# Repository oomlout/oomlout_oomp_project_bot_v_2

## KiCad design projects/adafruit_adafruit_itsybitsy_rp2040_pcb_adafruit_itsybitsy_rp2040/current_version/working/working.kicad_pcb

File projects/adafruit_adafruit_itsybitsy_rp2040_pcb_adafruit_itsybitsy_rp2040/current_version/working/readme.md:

# adafruit_itsybitsy_rp2040_pcb
 
## summary 
* id: adafruit_adafruit_itsybitsy_rp2040_pcb_adafruit_itsybitsy_rp2040
* user: adafruit
* name: adafruit_itsybitsy_rp2040_pcb
* board: adafruit_itsybitsy_rp2040
* repo: https://github.com/adafruit/Adafruit-ItsyBitsy-RP2040-PCB

* src_file_repo_sch: 
* src_file_repo_sch_link: https://github.com/adafruit/Adafruit-ItsyBitsy-RP2040-PCB/tree/main/
* full details link: https://github.com/oomlout/oomlout_oomp_project_bot_v_2/tree/main/projects/adafruit_adafruit_itsybitsy_rp2040_pcb_adafruit_itsybitsy_rp2040/current_version/working  

## schematic  
  
[schematic (pdf)](working_schematic.pdf) 

## pcb  

[board (pdf)](working.pdf)  

## working_bom
| Id | Designator | Footprint | Quantity | Designation | Supplier and ref |  | None | 
| --- | --- | --- | --- | --- | --- | --- | --- | 
| 1 | C11,C2 | _0603MP | 2 | 1uF |  |  | [''] | 
| 2 | C10,C3,C4,C13,C16,C12 | _0402NO | 6 | 0.1uF |  |  | [''] | 
| 3 | IC3 | QFN56_7MM_REDUCEDEPAD | 1 | RP2040_QFN56 |  |  | [''] | 
| 4 | U$35,U$34 | FIDUCIAL_1MM | 2 | FIDUCIAL_1MM |  |  | [''] | 
| 5 | D3,D1,D2 | SOD-323F | 3 | NSR0320 |  |  | [''] | 
| 6 | R5,R1 | _0402NO | 2 | 10K |  |  | [''] | 
| 7 | R4,R3 | _0402NO | 2 | 22 |  |  | [''] | 
| 8 | C6,C8 | 0805-NO | 2 | 10ÂµF |  |  | [''] | 
| 9 | L0 | CHIPLED_0603_NOOUTLINE | 1 | RED |  |  | [''] | 
| 10 | U1 | USON8_4X4 | 1 | GD25x16 |  |  | [''] | 
| 11 | JP4,JP2 | 1X14_ROUND70 | 2 |  |  |  | [''] | 
| 12 | R2 | _0402NO | 1 | 10k |  |  | [''] | 
| 13 | IC1 | SC70-5 | 1 | 74HCT1G125DBV |  |  | [''] | 
| 14 | C20,C19 | _0402NO | 2 | 22pF |  |  | [''] | 
| 15 | R11,R6,R7 | _0402NO | 3 | 1K |  |  | [''] | 
| 16 | U$4 | ITSY2040_TOP | 1 |  |  |  | [''] | 
| 17 | Y1 | CRYSTAL_2.5X2 | 1 | 12MHZ |  |  | [''] | 
| 18 | X3 | 4UCONN_20329_NARROW | 1 | microUSB |  |  | [''] | 
| 19 | SW3,SW2 | BTN_KMR2_4.6X2.8 | 2 | KMR2 |  |  | [''] | 
| 20 | U2 | SOT23-5 | 1 | AP2112K-3.3 |  |  | [''] | 
| 21 | JP1 | 1X05_ROUND_70 | 1 |  |  |  | [''] | 
| 22 | LED1 | SK6805_1515 | 1 | WS2812B_SK6805_1515 |  |  | [''] | 
| 23 | TP1 | TESTPOINT_ROUND_1.5MM_NO | 1 |  |  |  | [''] | 
| 24 | U$5 | ITSY2040_BOT | 1 |  |  |  | [''] | 

## bom_schematic
| Ref | Qnty | Value | Cmp name | Footprint | Description | Vendor | DNP | 
| --- | --- | --- | --- | --- | --- | --- | --- | 
| C2, C11 | 2 | 1uF | CAP_CERAMIC_0603MP | working:_0603MP |  |  |  | 
| C3, C4, C10, C12, C13, C16 | 6 | 0.1uF | CAP_CERAMIC_0402NO | working:_0402NO |  |  |  | 
| C6, C8 | 2 | 10ÂµF | CAP_CERAMIC0805-NOOUTLINE | working:0805-NO |  |  |  | 
| C19, C20 | 2 | 22pF | CAP_CERAMIC_0402NO | working:_0402NO |  |  |  | 
| D1, D2, D3 | 3 | NSR0320 | DIODESOD-323F | working:SOD-323F |  |  |  | 
| IC1 | 1 | 741G125DCK | 741G125DCK | working:SC70-5 |  |  |  | 
| IC3 | 1 | RP2040_QFN56 | RP2040_QFN56 | working:QFN56_7MM_REDUCEDEPAD |  |  |  | 
| JP1 | 1 | HEADER-1X570MIL | HEADER-1X570MIL | working:1X05_ROUND_70 |  |  |  | 
| JP2, JP4 | 2 | HEADER-1X14 | HEADER-1X14 | working:1X14_ROUND70 |  |  |  | 
| L0 | 1 | RED | LED0603_NOOUTLINE | working:CHIPLED_0603_NOOUTLINE |  |  |  | 
| LED1 | 1 | WS2812B_SK6805_1515 | WS2812B_SK6805_1515 | working:SK6805_1515 |  |  |  | 
| R1, R5 | 2 | 10K | RESISTOR_0402NO | working:_0402NO |  |  |  | 
| R2 | 1 | 10k | RESISTOR_0402NO | working:_0402NO |  |  |  | 
| R3, R4 | 2 | 22 | RESISTOR_0402NO | working:_0402NO |  |  |  | 
| R6, R7, R11 | 3 | 1K | RESISTOR_0402NO | working:_0402NO |  |  |  | 
| SW2, SW3 | 2 | KMR2 | SWITCH_TACT_SMT4.6X2.8 | working:BTN_KMR2_4.6X2.8 |  |  |  | 
| TP1 | 1 | TESTPOINTROUND1.5MMNO | TESTPOINTROUND1.5MMNO | working:TESTPOINT_ROUND_1.5MM_NO |  |  |  | 
| U1 | 1 | GD25x16 | SPIFLASH_8PIN_4X4 | working:USON8_4X4 |  |  |  | 
| U2 | 1 | AP2112K-3.3 | VREG_SOT23-5 | working:SOT23-5 |  |  |  | 
| U$34, U$35 | 2 | FIDUCIAL_1MM | FIDUCIAL_1MM | working:FIDUCIAL_1MM |  |  |  | 
| X3 | 1 | microUSB | USB_MICRO_NARROW | working:4UCONN_20329_NARROW |  |  |  | 
| Y1 | 1 | 12MHZ | CRYSTAL2.5X2.0 | working:CRYSTAL_2.5X2 |  |  |  |

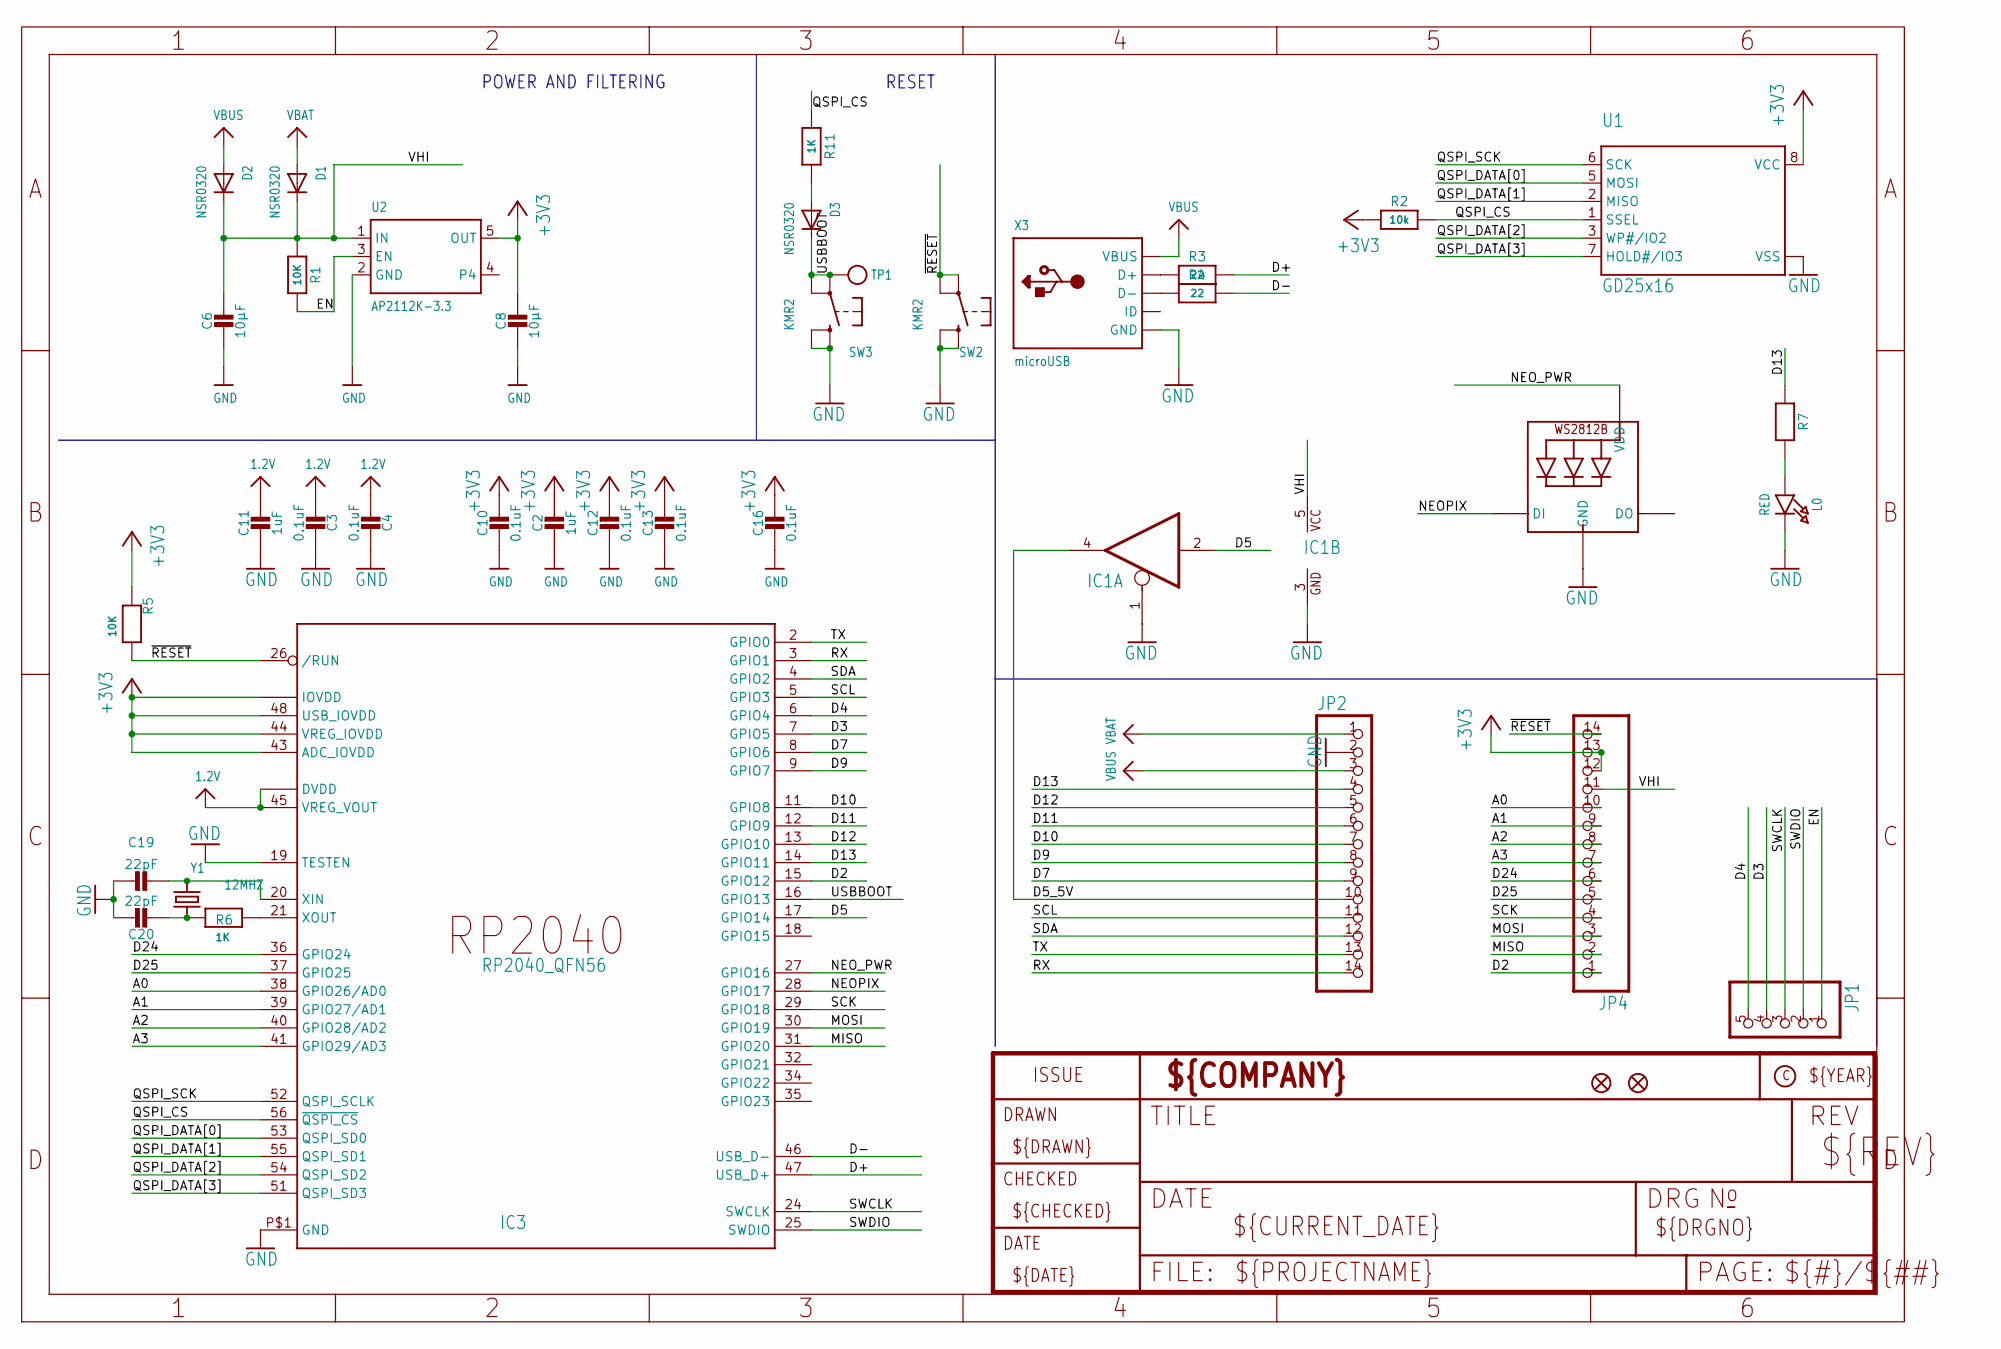
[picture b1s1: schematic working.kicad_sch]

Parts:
C2, C11: 1uF; _0603MP
C3, C4, C10, C12, C13, C16: 0.1uF; _0402NO
C6, C8: 10µF; 0805-NO
C19, C20: 22pF; _0402NO
D1, D2, D3: NSR0320; SOD-323F
IC1: 741G125DCK; SC70-5
IC3: RP2040_QFN56; QFN56_7MM_REDUCEDEPAD
JP1: HEADER-1X570MIL; 1X05_ROUND_70
JP2, JP4: HEADER-1X14; 1X14_ROUND70
L0: RED; CHIPLED_0603_NOOUTLINE
LED1: WS2812B_SK6805_1515; SK6805_1515
R1, R5: 10K; _0402NO
R2: 10k; _0402NO
R3, R4: 22; _0402NO
R6, R7, R11: 1K; _0402NO
SW2, SW3: KMR2; BTN_KMR2_4.6X2.8
TP1: TESTPOINTROUND1.5MMNO; TESTPOINT_ROUND_1.5MM_NO
U1: GD25x16; USON8_4X4
U2: AP2112K-3.3; SOT23-5
U$34, U$35: FIDUCIAL_1MM
X3: microUSB; 4UCONN_20329_NARROW
Y1: 12MHZ; CRYSTAL_2.5X2

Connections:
1.2V: C3.2, C4.2, C11.1, IC3.23 (DVDD), IC3.45 (VREG_VOUT), IC3.50 (DVDD)
+3V3: C2.1, C8.1, C10.1, C12.1, C13.1, C16.1, IC3.1 (IOVDD), IC3.10 (IOVDD), IC3.22 (IOVDD), IC3.33 (IOVDD), IC3.42 (IOVDD), IC3.43 (ADC_IOVDD), IC3.44 (VREG_IOVDD), IC3.48 (USB_IOVDD), IC3.49 (IOVDD), JP4.12, JP4.13, R2.1, R5.1, U1.8 (VCC), U2.5 (OUT)
A0: IC3.38 (GPIO26/AD0), JP4.10
A1: IC3.39 (GPIO27/AD1), JP4.9
A2: IC3.40 (GPIO28/AD2), JP4.8
A3: IC3.41 (GPIO29/AD3), JP4.7
D2: IC3.15 (GPIO12), JP4.1
D3: IC3.7 (GPIO5), JP1.4
D4: IC3.6 (GPIO4), JP1.5
D5: IC1.2 (I), IC3.17 (GPIO14)
D5_5V: IC1.4 (O), JP2.10
D7: IC3.8 (GPIO6), JP2.9
D9: IC3.9 (GPIO7), JP2.8
D10: IC3.11 (GPIO8), JP2.7
D11: IC3.12 (GPIO9), JP2.6
D12: IC3.13 (GPIO10), JP2.5
D13: IC3.14 (GPIO11), JP2.4, R7.1
D24: IC3.36 (GPIO24), JP4.6
D25: IC3.37 (GPIO25), JP4.5
D+: IC3.47 (USB_D+), R3.2
D-: IC3.46 (USB_D-), R4.2
EN: JP1.1, R1.2, U2.3 (EN)
GND: C2.2, C3.1, C4.1, C6.2, C8.2, C10.2, C11.2, C12.2, C13.2, C16.2, C19.1, C20.1, IC1.1 (OE), IC1.3 (GND), IC3.19 (TESTEN), IC3.P$1 (GND), JP2.2, L0.C, LED1.4 (GND), SW2.B (S), SW2.B' (S1), SW3.B (S), SW3.B' (S1), U1.4 (VSS), U1.PAD (VSS), U2.2 (GND), X3.BASE@1 (GND), X3.BASE@2 (GND), X3.GND, X3.SPRT@1 (GND), X3.SPRT@2 (GND), X3.SPRT@3 (GND), X3.SPRT@4 (GND)
MISO: IC3.31 (GPIO20), JP4.2
MOSI: IC3.30 (GPIO19), JP4.3
unnamed: R3.1, X3.D+
unnamed: L0.A, R7.2
unnamed: R4.1, X3.D-
unnamed: D3.A, R11.2
unnamed: C19.2, IC3.20 (XIN), Y1.3 (2)
unnamed: C20.2, R6.1, Y1.1
unnamed: IC3.21 (XOUT), R6.2
NEOPIX: IC3.28 (GPIO17), LED1.1 (DI)
NEO_PWR: IC3.27 (GPIO16), LED1.2 (VDD)
QSPI_CS: IC3.56 (~QSPI_CS), R2.2, R11.1, U1.1 (SSEL)
QSPI_DATA[0]: IC3.53 (QSPI_SD0), U1.5 (MOSI)
QSPI_DATA[1]: IC3.55 (QSPI_SD1), U1.2 (MISO)
QSPI_DATA[2]: IC3.54 (QSPI_SD2), U1.3 (WP#/IO2)
QSPI_DATA[3]: IC3.51 (QSPI_SD3), U1.7 (HOLD#/IO3)
QSPI_SCK: IC3.52 (QSPI_SCLK), U1.6 (SCK)
RX: IC3.3 (GPIO1), JP2.14
SCK: IC3.29 (GPIO18), JP4.4
SCL: IC3.5 (GPIO3), JP2.11
SDA: IC3.4 (GPIO2), JP2.12
SWCLK: IC3.24 (SWCLK), JP1.3
SWDIO: IC3.25 (SWDIO), JP1.2
TX: IC3.2 (GPIO0), JP2.13
USBBOOT: D3.C, IC3.16 (GPIO13), SW3.A, SW3.A' (P1), TP1.P$1
VBAT: D1.A, JP2.1
VBUS: D2.A, JP2.3, X3.VBUS
VHI: C6.1, D1.C, D2.C, IC1.5 (VCC), JP4.11, R1.1, U2.1 (IN)
~RESET: IC3.26 (/RUN), JP4.14, R5.2, SW2.A, SW2.A' (P1)

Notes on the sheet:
POWER AND FILTERING
RESET

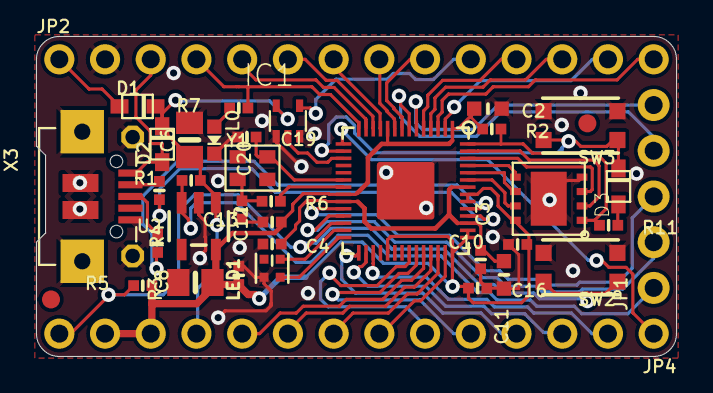
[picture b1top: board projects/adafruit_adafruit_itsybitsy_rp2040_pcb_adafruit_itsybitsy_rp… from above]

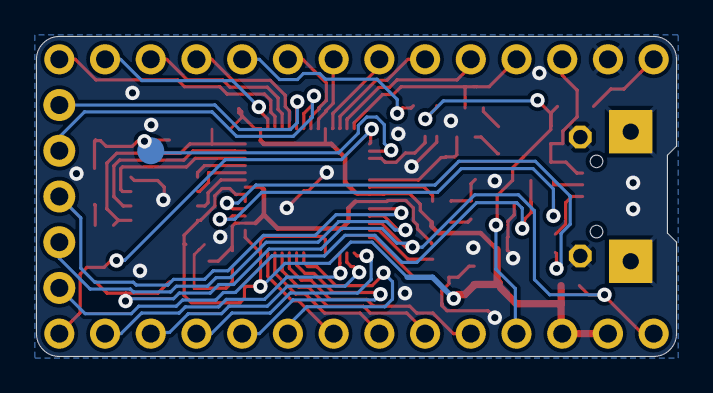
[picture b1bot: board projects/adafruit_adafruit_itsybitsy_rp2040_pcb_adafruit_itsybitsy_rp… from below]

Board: 4 copper layers, 35.6 x 17.8 mm, 41 parts (2 on the bottom side), 52 nets.

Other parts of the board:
U$4: ITSY2040_TOP
U$5: ITSY2040_BOT

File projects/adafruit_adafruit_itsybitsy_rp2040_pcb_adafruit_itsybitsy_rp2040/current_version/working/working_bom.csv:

"Id";"Designator";"Footprint";"Quantity";"Designation";"Supplier and ref";
1;"C11,C2";"_0603MP";2;"1uF";;;
2;"C10,C3,C4,C13,C16,C12";"_0402NO";6;"0.1uF";;;
3;"IC3";"QFN56_7MM_REDUCEDEPAD";1;"RP2040_QFN56";;;
4;"U$35,U$34";"FIDUCIAL_1MM";2;"FIDUCIAL_1MM";;;
5;"D3,D1,D2";"SOD-323F";3;"NSR0320";;;
6;"R5,R1";"_0402NO";2;"10K";;;
7;"R4,R3";"_0402NO";2;"22";;;
8;"C6,C8";"0805-NO";2;"10µF";;;
9;"L0";"CHIPLED_0603_NOOUTLINE";1;"RED";;;
10;"U1";"USON8_4X4";1;"GD25x16";;;
11;"JP4,JP2";"1X14_ROUND70";2;"";;;
12;"R2";"_0402NO";1;"10k";;;
13;"IC1";"SC70-5";1;"74HCT1G125DBV";;;
14;"C20,C19";"_0402NO";2;"22pF";;;
15;"R11,R6,R7";"_0402NO";3;"1K";;;
16;"U$4";"ITSY2040_TOP";1;"";;;
17;"Y1";"CRYSTAL_2.5X2";1;"12MHZ";;;
18;"X3";"4UCONN_20329_NARROW";1;"microUSB";;;
19;"SW3,SW2";"BTN_KMR2_4.6X2.8";2;"KMR2";;;
20;"U2";"SOT23-5";1;"AP2112K-3.3";;;
21;"JP1";"1X05_ROUND_70";1;"";;;
22;"LED1";"SK6805_1515";1;"WS2812B_SK6805_1515";;;
23;"TP1";"TESTPOINT_ROUND_1.5MM_NO";1;"";;;
24;"U$5";"ITSY2040_BOT";1;"";;;

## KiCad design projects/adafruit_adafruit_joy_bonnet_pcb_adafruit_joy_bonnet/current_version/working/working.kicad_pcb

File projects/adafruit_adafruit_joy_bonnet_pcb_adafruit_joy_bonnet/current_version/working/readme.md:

# adafruit_joy_bonnet_pcb
 
## summary 
* id: adafruit_adafruit_joy_bonnet_pcb_adafruit_joy_bonnet
* user: adafruit
* name: adafruit_joy_bonnet_pcb
* board: adafruit_joy_bonnet
* repo: https://github.com/adafruit/Adafruit-Joy-Bonnet-PCB

* src_file_repo_sch: 
* src_file_repo_sch_link: https://github.com/adafruit/Adafruit-Joy-Bonnet-PCB/tree/master/
* full details link: https://github.com/oomlout/oomlout_oomp_project_bot_v_2/tree/main/projects/adafruit_adafruit_joy_bonnet_pcb_adafruit_joy_bonnet/current_version/working  

## schematic  
  
[schematic (pdf)](working_schematic.pdf) 

## pcb  

[board (pdf)](working.pdf)  

## working_bom
| Id | Designator | Footprint | Quantity | Designation | Supplier and ref |  | None | 
| --- | --- | --- | --- | --- | --- | --- | --- | 
| 1 | U1 | MSOP10 | 1 | ADS1015 |  |  | [''] | 
| 2 | FID3,FID2 | FIDUCIAL_1MM | 2 | FIDUCIAL_1MM |  |  | [''] | 
| 3 | SW1,SW8,SW5,SW3,SW4,SW2 | EVQ-Q2_SMALLER | 6 | EVQQ |  |  | [''] | 
| 4 | RPI1 | PI_BONNET_SMT | 1 | RASPBERRYPI_BPLUS_BONNETSMT |  |  | [''] | 
| 5 | UNK2,UNK1 | BTN_KMR2_4.6X2.8 | 2 | KMR2 |  |  | [''] | 
| 6 | JOY1 | JOYSTICK_ANALOG_MINITHM | 1 | JOYSTICK_ANALOG_XY |  |  | [''] | 
| 7 | U$7 | PCBFEAT-REV-040 | 1 |  |  |  | [''] | 

## bom_schematic
| Ref | Qnty | Value | Cmp name | Footprint | Description | Vendor | DNP | 
| --- | --- | --- | --- | --- | --- | --- | --- | 
| FID2, FID3 | 2 | FIDUCIAL_1MM | FIDUCIAL_1MM | working:FIDUCIAL_1MM |  |  |  | 
| JOY1 | 1 | JOYSTICK_ANALOG_XY | JOYSTICK_ANALOG_XY | working:JOYSTICK_ANALOG_MINITHM |  |  |  | 
| RPI1 | 1 | RASPBERRYPI_BPLUS_BONNETSMT | RASPBERRYPI_BPLUS_BONNETSMT | working:PI_BONNET_SMT |  |  |  | 
| SW1, SW2, SW3, SW4, SW5, SW8 | 6 | EVQQ | SWITCH_TACT_SMT_EVQQ2_SMALL | working:EVQ-Q2_SMALLER |  |  |  | 
| U1 | 1 | ADS1015 | ADC_ADS1015 | working:MSOP10 |  |  |  | 
| UNK1, UNK2 | 2 | KMR2 | SWITCH_TACT_SMT4.6X2.8 | working:BTN_KMR2_4.6X2.8 |  |  |  |

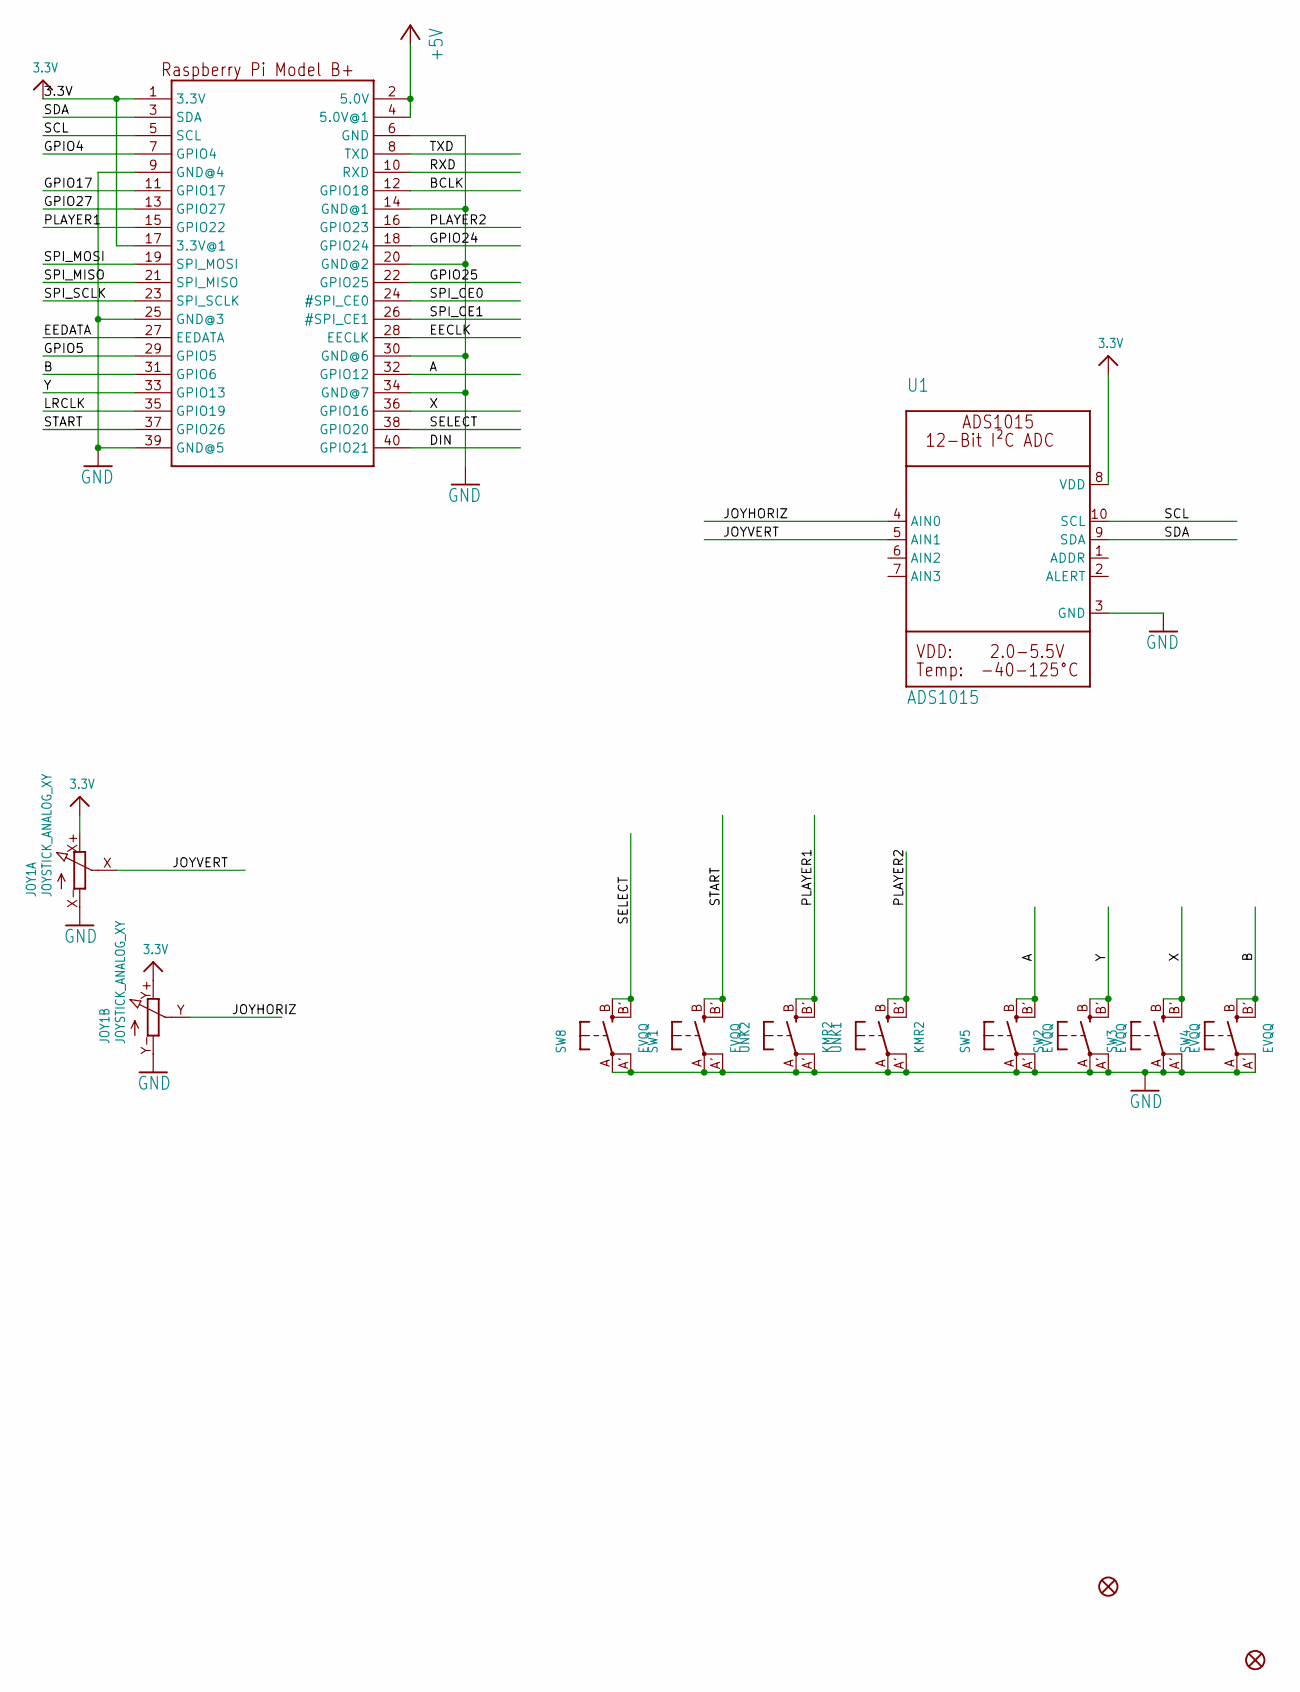
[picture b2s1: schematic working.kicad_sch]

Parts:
FID2, FID3: FIDUCIAL_1MM
JOY1: JOYSTICK_ANALOG_XY; JOYSTICK_ANALOG_MINITHM
RPI1: RASPBERRYPI_BPLUS_BONNETSMT; PI_BONNET_SMT
SW1, SW2, SW3, SW4, SW5, SW8: EVQQ; EVQ-Q2_SMALLER
U1: ADS1015; MSOP10
UNK1, UNK2: KMR2; BTN_KMR2_4.6X2.8

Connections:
3.3V: JOY1.X+ (E), JOY1.Y+ (E), RPI1.1 (3.3V), RPI1.17 (3.3V@1), U1.8 (VDD)
+5V: RPI1.2 (5.0V), RPI1.4 (5.0V@1)
A: RPI1.32 (GPIO12), SW5.B (S), SW5.B' (S1)
B: RPI1.31 (GPIO6), SW4.B (S), SW4.B' (S1)
BCLK: RPI1.12 (GPIO18)
DIN: RPI1.40 (GPIO21)
EECLK: RPI1.28 (EECLK)
EEDATA: RPI1.27 (EEDATA)
GND: JOY1.X- (A), JOY1.Y- (A), RPI1.6 (GND), RPI1.9 (GND@4), RPI1.14 (GND@1), RPI1.20 (GND@2), RPI1.25 (GND@3), RPI1.30 (GND@6), RPI1.34 (GND@7), RPI1.39 (GND@5), SW1.A, SW1.A' (P1), SW2.A, SW2.A' (P1), SW3.A, SW3.A' (P1), SW4.A, SW4.A' (P1), SW5.A, SW5.A' (P1), SW8.A, SW8.A' (P1), U1.3 (GND), UNK1.A, UNK1.A' (P1), UNK2.A, UNK2.A' (P1)
GPIO4: RPI1.7 (GPIO4)
GPIO5: RPI1.29 (GPIO5)
GPIO17: RPI1.11 (GPIO17)
GPIO24: RPI1.18 (GPIO24)
GPIO25: RPI1.22 (GPIO25)
GPIO27: RPI1.13 (GPIO27)
JOYHORIZ: JOY1.Y (S), U1.4 (AIN0)
JOYVERT: JOY1.X (S), U1.5 (AIN1)
LRCLK: RPI1.35 (GPIO19)
PLAYER1: RPI1.15 (GPIO22), UNK2.B (S), UNK2.B' (S1)
PLAYER2: RPI1.16 (GPIO23), UNK1.B (S), UNK1.B' (S1)
RXD: RPI1.10 (RXD)
SCL: RPI1.5 (SCL), U1.10 (SCL)
SDA: RPI1.3 (SDA), U1.9 (SDA)
SELECT: RPI1.38 (GPIO20), SW8.B (S), SW8.B' (S1)
SPI_CE0: RPI1.24 (#SPI_CE0)
SPI_CE1: RPI1.26 (#SPI_CE1)
SPI_MISO: RPI1.21 (SPI_MISO)
SPI_MOSI: RPI1.19 (SPI_MOSI)
SPI_SCLK: RPI1.23 (SPI_SCLK)
START: RPI1.37 (GPIO26), SW1.B (S), SW1.B' (S1)
TXD: RPI1.8 (TXD)
X: RPI1.36 (GPIO16), SW3.B (S), SW3.B' (S1)
Y: RPI1.33 (GPIO13), SW2.B (S), SW2.B' (S1)

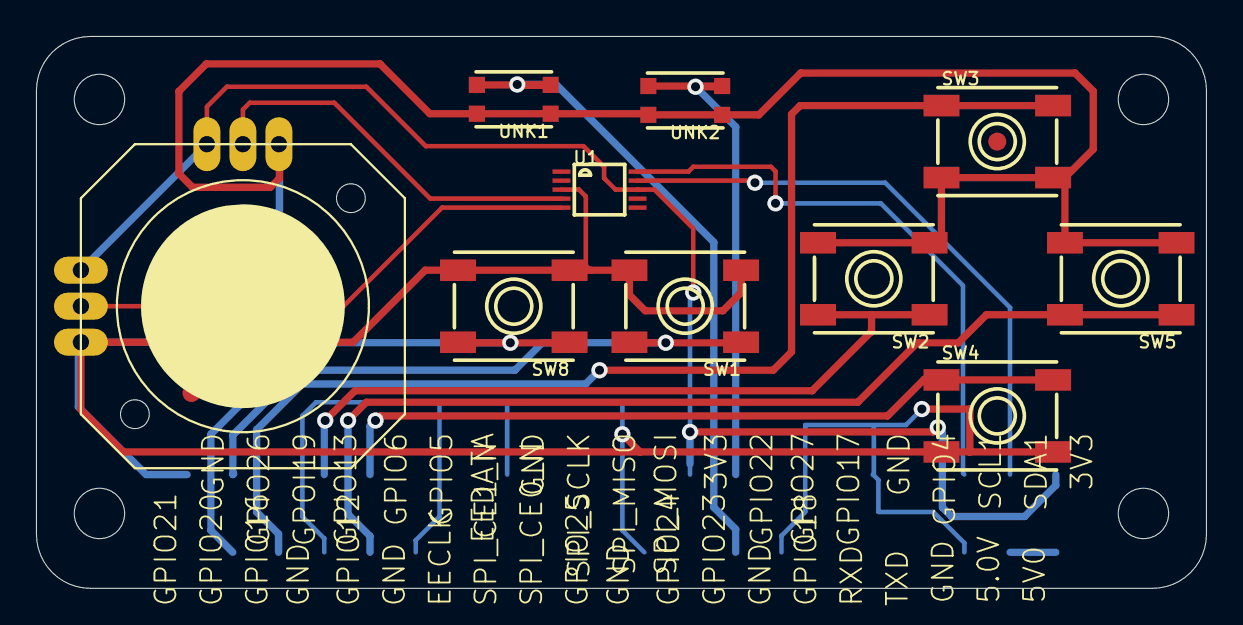
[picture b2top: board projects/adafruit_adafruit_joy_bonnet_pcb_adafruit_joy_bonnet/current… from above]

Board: 2 copper layers, 65.0 x 30.7 mm, 14 parts (1 on the bottom side), 15 nets.

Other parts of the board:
U$7: PCBFEAT-REV-040

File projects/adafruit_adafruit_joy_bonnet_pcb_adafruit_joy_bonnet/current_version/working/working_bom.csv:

"Id";"Designator";"Footprint";"Quantity";"Designation";"Supplier and ref";
1;"U1";"MSOP10";1;"ADS1015";;;
2;"FID3,FID2";"FIDUCIAL_1MM";2;"FIDUCIAL_1MM";;;
3;"SW1,SW8,SW5,SW3,SW4,SW2";"EVQ-Q2_SMALLER";6;"EVQQ";;;
4;"RPI1";"PI_BONNET_SMT";1;"RASPBERRYPI_BPLUS_BONNETSMT";;;
5;"UNK2,UNK1";"BTN_KMR2_4.6X2.8";2;"KMR2";;;
6;"JOY1";"JOYSTICK_ANALOG_MINITHM";1;"JOYSTICK_ANALOG_XY";;;
7;"U$7";"PCBFEAT-REV-040";1;"";;;

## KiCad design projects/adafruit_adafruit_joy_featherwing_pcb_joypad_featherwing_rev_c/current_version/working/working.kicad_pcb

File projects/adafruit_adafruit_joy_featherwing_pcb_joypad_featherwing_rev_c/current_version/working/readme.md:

# adafruit_joy_featherwing_pcb
 
## summary 
* id: adafruit_adafruit_joy_featherwing_pcb_joypad_featherwing_rev_c
* user: adafruit
* name: adafruit_joy_featherwing_pcb
* board: joypad_featherwing_rev_c
* repo: https://github.com/adafruit/Adafruit-Joy-Featherwing-PCB

* src_file_repo_sch: 
* src_file_repo_sch_link: https://github.com/adafruit/Adafruit-Joy-Featherwing-PCB/tree/master/
* full details link: https://github.com/oomlout/oomlout_oomp_project_bot_v_2/tree/main/projects/adafruit_adafruit_joy_featherwing_pcb_joypad_featherwing_rev_c/current_version/working  

## schematic  
  
[schematic (pdf)](working_schematic.pdf) 

## pcb  

[board (pdf)](working.pdf)  

## working_bom
| Id | Designator | Footprint | Quantity | Designation | Supplier and ref |  | None | 
| --- | --- | --- | --- | --- | --- | --- | --- | 
| 1 | U$9,U$11 | ADAFRUIT_5MM | 2 |  |  |  | [''] | 
| 2 | SW6,SW7 | BTN_KMR2_4.6X2.8 | 2 | KMR2 |  |  | [''] | 
| 3 | IC1 | QFN24_4MM | 1 | ATSAMD09D14A-MU |  |  | [''] | 
| 4 | RIGHT0,UP0,LEFT0,DOWN0 | EVQ-Q2_SMALLER | 4 | 6mm |  |  | [''] | 
| 5 | FID1,FID2 | FIDUCIAL_1MM | 2 | FIDUCIAL_1MM |  |  | [''] | 
| 6 | D1 | CHIPLED_0805_NOOUTLINE | 1 | RED |  |  | [''] | 
| 7 | R3 | 0603-NO | 1 | 10K |  |  | [''] | 
| 8 | R4 | 0603-NO | 1 | 10k |  |  | [''] | 
| 9 | R2,R5 | 0603-NO | 2 | 1k |  |  | [''] | 
| 10 | MS1 | FEATHERWING | 1 | FEATHERWING |  |  | [''] | 
| 11 | JOY1 | JOYSTICK_ANALOG_MINITHM | 1 | JOYSTICK_ANALOG_XY |  |  | [''] | 
| 12 | SJ9,SJ7,SJ2,SJ3,SJ4,SJ8,SJ6,SJ5,SJ1 | SOLDERJUMPER_ARROW_NOPASTE | 9 |  |  |  | [''] | 
| 13 | TP1,TP2 | TESTPOINT_ROUND_2MM | 2 |  |  |  | [''] | 
| 14 | U$7 | PCBFEAT-REV-040 | 1 |  |  |  | [''] | 
| 15 | U$10 | FEATHERLOGO_MED | 1 |  |  |  | [''] | 
| 16 | U$12 | SEESAW_LOGO | 1 |  |  |  | [''] | 

## bom_schematic
| Ref | Qnty | Value | Cmp name | Footprint | Description | Vendor | DNP | 
| --- | --- | --- | --- | --- | --- | --- | --- | 
| D1 | 1 | RED | LED0805_NOOUTLINE | working:CHIPLED_0805_NOOUTLINE |  |  |  | 
| DOWN0 | 1 | 6mm | SWITCH_TACT_SMT_EVQQ2_SMALL | working:EVQ-Q2_SMALLER |  |  |  | 
| FID1, FID2 | 2 | FIDUCIAL_1MM | FIDUCIAL_1MM | working:FIDUCIAL_1MM |  |  |  | 
| IC1 | 1 | ATSAMD09D14A-MU | ATSAMD09D14A-MU | working:QFN24_4MM |  |  |  | 
| JOY1 | 1 | JOYSTICK_ANALOG_XY | JOYSTICK_ANALOG_XY | working:JOYSTICK_ANALOG_MINITHM |  |  |  | 
| LEFT0 | 1 | 6mm | SWITCH_TACT_SMT_EVQQ2_SMALL | working:EVQ-Q2_SMALLER |  |  |  | 
| MS1 | 1 | FEATHERWING | FEATHERWING | working:FEATHERWING |  |  |  | 
| R2, R5 | 2 | 1k | RESISTOR_0603_NOOUT | working:0603-NO |  |  |  | 
| R3 | 1 | 10K | RESISTOR_0603_NOOUT | working:0603-NO |  |  |  | 
| R4 | 1 | 10k | RESISTOR_0603_NOOUT | working:0603-NO |  |  |  | 
| RIGHT0 | 1 | 6mm | SWITCH_TACT_SMT_EVQQ2_SMALL | working:EVQ-Q2_SMALLER |  |  |  | 
| SJ1, SJ2, SJ3, SJ4, SJ5, SJ6, SJ7, SJ8, SJ9 | 9 | SOLDERJUMPER | SOLDERJUMPER | working:SOLDERJUMPER_ARROW_NOPASTE |  |  |  | 
| SW6, SW7 | 2 | KMR2 | SWITCH_TACT_SMT4.6X2.8 | working:BTN_KMR2_4.6X2.8 |  |  |  | 
| TP1, TP2 | 2 | TESTPOINTROUND2MM | TESTPOINTROUND2MM | working:TESTPOINT_ROUND_2MM |  |  |  | 
| UP0 | 1 | 6mm | SWITCH_TACT_SMT_EVQQ2_SMALL | working:EVQ-Q2_SMALLER |  |  |  |

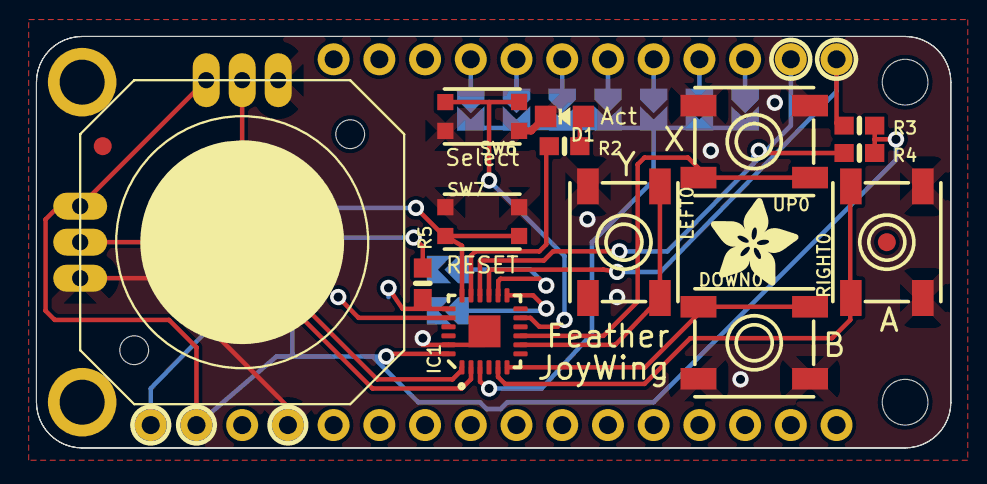
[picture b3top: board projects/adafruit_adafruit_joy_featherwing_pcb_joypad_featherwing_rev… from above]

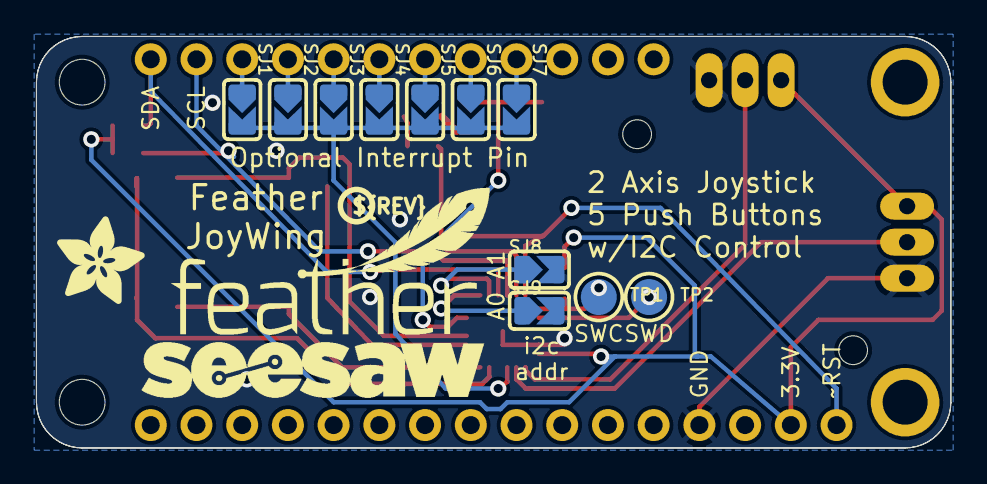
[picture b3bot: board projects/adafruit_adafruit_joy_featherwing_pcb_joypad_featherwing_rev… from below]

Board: 16 copper layers, 50.8 x 22.9 mm, 32 parts (15 on the bottom side), 26 nets.

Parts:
D1: RED; CHIPLED_0805_NOOUTLINE
DOWN0: 6mm; EVQ-Q2_SMALLER
FID1, FID2: FIDUCIAL_1MM
IC1: ATSAMD09D14A-MU; QFN24_4MM
JOY1: JOYSTICK_ANALOG_XY; JOYSTICK_ANALOG_MINITHM
LEFT0: 6mm; EVQ-Q2_SMALLER
MS1: FEATHERWING
R2, R5: 1k; 0603-NO
R3: 10K; 0603-NO
R4: 10k; 0603-NO
RIGHT0: 6mm; EVQ-Q2_SMALLER
SJ1, SJ2, SJ3, SJ4, SJ5, SJ6, SJ7, SJ8, SJ9: SOLDERJUMPER_ARROW_NOPASTE
SW6, SW7: KMR2; BTN_KMR2_4.6X2.8
TP1, TP2: TESTPOINT_ROUND_2MM
U$7: PCBFEAT-REV-040
U$9, U$11: ADAFRUIT_5MM
U$10: FEATHERLOGO_MED
U$12: SEESAW_LOGO
UP0: 6mm; EVQ-Q2_SMALLER

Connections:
3.3V: IC1.24, JOY1.X+, JOY1.Y+, MS1.2, R3.2, R4.2, R5.2
GND: D1.C, DOWN0.A, DOWN0.A', IC1.23, IC1.THERM, JOY1.X-, JOY1.Y-, LEFT0.A, LEFT0.A', MS1.4, RIGHT0.A, RIGHT0.A', SJ8.2, SJ9.2, SW6.A, SW6.A', SW7.A, SW7.A', UP0.A, UP0.A'
unnamed: MS1.19, SJ1.1
unnamed: MS1.20, SJ2.1
unnamed: MS1.21, SJ3.1
unnamed: MS1.22, SJ4.1
unnamed: IC1.17, R2.1
unnamed: MS1.23, SJ5.1
unnamed: MS1.24, SJ6.1
unnamed: MS1.25, SJ7.1
unnamed: D1.A, R2.2
PA02_A0: IC1.1, JOY1.Y
PA03_A1: IC1.2, JOY1.X
PA04_A2: IC1.3, SJ1.2, SJ2.2, SJ3.2, SJ4.2, SJ5.2, SJ6.2, SJ7.2
PA06_A4: IC1.5, RIGHT0.B, RIGHT0.B'
PA07_A5: DOWN0.B, DOWN0.B', IC1.6
PA09_XOSC: IC1.8, LEFT0.B, LEFT0.B'
PA10_A18: IC1.9, UP0.B, UP0.B'
PA14: IC1.11, SW6.B, SW6.B'
PA16_D16: IC1.13, SJ9.1
PA17_D17: IC1.14, SJ8.1
PA22_SDA: IC1.15, MS1.17, R3.1
PA23_SCL: IC1.16, MS1.18, R4.1
SWCLK: IC1.19, R5.1, TP1.P$1
SWDIO: IC1.20, TP2.P$1
~RESET: IC1.18, MS1.1, SW7.B, SW7.B'

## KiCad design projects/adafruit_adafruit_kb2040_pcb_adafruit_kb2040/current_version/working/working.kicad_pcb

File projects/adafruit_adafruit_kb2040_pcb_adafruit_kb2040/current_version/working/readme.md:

# adafruit_kb2040_pcb
 
## summary 
* id: adafruit_adafruit_kb2040_pcb_adafruit_kb2040
* user: adafruit
* name: adafruit_kb2040_pcb
* board: adafruit_kb2040
* repo: https://github.com/adafruit/Adafruit-KB2040-PCB

* src_file_repo_sch: 
* src_file_repo_sch_link: https://github.com/adafruit/Adafruit-KB2040-PCB/tree/main/
* full details link: https://github.com/oomlout/oomlout_oomp_project_bot_v_2/tree/main/projects/adafruit_adafruit_kb2040_pcb_adafruit_kb2040/current_version/working  

## schematic  
  
[schematic (pdf)](working_schematic.pdf) 

## pcb  

[board (pdf)](working.pdf)  

## working_bom
| Id | Designator | Footprint | Quantity | Designation | Supplier and ref |  | None | 
| --- | --- | --- | --- | --- | --- | --- | --- | 
| 1 | R9,R5,R7 | _0402NO | 3 | 10K |  |  | [''] | 
| 2 | C10,C12 | _0603MP | 2 | 1uF |  |  | [''] | 
| 3 | Y1 | CRYSTAL_2.5X2 | 1 | 12MHZ |  |  | [''] | 
| 4 | D1,D3 | SOD-323F | 2 | NSR0320 |  |  | [''] | 
| 5 | SW2,SW3 | BTN_KMR2_4.6X2.8 | 2 | KMR2 |  |  | [''] | 
| 6 | C8,C6 | _0805MP | 2 | 10ÂµF |  |  | [''] | 
| 7 | U2 | SOT23-5 | 1 | AP2112K-3.3 |  |  | [''] | 
| 8 | U$19 | KB2040_TOP | 1 |  |  |  | [''] | 
| 9 | U5 | USON8_4X4 | 1 | 8MB QSPI Flash |  |  | [''] | 
| 10 | R10,R2,R1,R12 | _0402NO | 4 | 5.1K |  |  | [''] | 
| 11 | IC2 | QFN56_7MM_REDUCEDEPAD | 1 | RP2040_QFN56 |  |  | [''] | 
| 12 | R8 | 0805-NO | 1 | FUSE |  |  | [''] | 
| 13 | U$34,U$35 | FIDUCIAL_1MM | 2 | FIDUCIAL_1MM |  |  | [''] | 
| 14 | R11,R6 | _0402NO | 2 | 1K |  |  | [''] | 
| 15 | JP2,JP1 | 1X13_CASTEL | 2 |  |  |  | [''] | 
| 16 | C15 | 0603-NO | 1 | 1uF |  |  | [''] | 
| 17 | D2 | CHIPLED_0603_NOOUTLINE | 1 | GREEN |  |  | [''] | 
| 18 | C11,C17,C14,C7,C16,C13,C9 | _0402NO | 7 | 0.1uF |  |  | [''] | 
| 19 | R3,R4 | _0402NO | 2 | 27 |  |  | [''] | 
| 20 | C19,C20 | _0402NO | 2 | 22pF |  |  | [''] | 
| 21 | LED1 | SK6805_1515 | 1 | WS2812B_SK6805_1515 |  |  | [''] | 
| 22 | X6 | USB_C_CUSB31-CFM2AX-01-X | 1 | USB TYPE C |  |  | [''] | 
| 23 | CONN1 | JST_SH4_SKINNY | 1 | STEMMA_I2C_QTSKINNY |  |  | [''] | 
| 24 | SJ1 | SOLDERJUMPER_ARROW_NOPASTE | 1 |  |  |  | [''] | 
| 25 | TP1 | TESTPOINT_ROUND_1.5MM_NO | 1 |  |  |  | [''] | 
| 26 | U$17 | KB2040_BOT | 1 |  |  |  | [''] | 
| 27 | U$20 | PCBFEAT-REV-040 | 1 |  |  |  | [''] | 

## bom_schematic
| Ref | Qnty | Value | Cmp name | Footprint | Description | Vendor | DNP | 
| --- | --- | --- | --- | --- | --- | --- | --- | 
| C6, C8 | 2 | 10ÂµF | CAP_CERAMIC_0805MP | working:_0805MP |  |  |  | 
| C7, C9, C11, C13, C14, C16, C17 | 7 | 0.1uF | CAP_CERAMIC_0402NO | working:_0402NO |  |  |  | 
| C10, C12 | 2 | 1uF | CAP_CERAMIC_0603MP | working:_0603MP |  |  |  | 
| C15 | 1 | 1uF | CAP_CERAMIC0603_NO | working:0603-NO |  |  |  | 
| C19, C20 | 2 | 22pF | CAP_CERAMIC_0402NO | working:_0402NO |  |  |  | 
| CONN1 | 1 | STEMMA_I2C_QTSKINNY | STEMMA_I2C_QTSKINNY | working:JST_SH4_SKINNY |  |  |  | 
| D1, D3 | 2 | NSR0320 | DIODESOD-323F | working:SOD-323F |  |  |  | 
| D2 | 1 | GREEN | LED0603_NOOUTLINE | working:CHIPLED_0603_NOOUTLINE |  |  |  | 
| IC2 | 1 | RP2040_QFN56 | RP2040_QFN56 | working:QFN56_7MM_REDUCEDEPAD |  |  |  | 
| JP1, JP2 | 2 | HEADER-1X13_CASTEL | HEADER-1X13_CASTEL | working:1X13_CASTEL |  |  |  | 
| LED1 | 1 | WS2812B_SK6805_1515 | WS2812B_SK6805_1515 | working:SK6805_1515 |  |  |  | 
| R1, R2, R10, R12 | 4 | 5.1K | RESISTOR_0402NO | working:_0402NO |  |  |  | 
| R3, R4 | 2 | 27 | RESISTOR_0402NO | working:_0402NO |  |  |  | 
| R5, R7, R9 | 3 | 10K | RESISTOR_0402NO | working:_0402NO |  |  |  | 
| R6, R11 | 2 | 1K | RESISTOR_0402NO | working:_0402NO |  |  |  | 
| R8 | 1 | FUSE | RESISTOR0805_NOOUTLINE | working:0805-NO |  |  |  | 
| SJ1 | 1 | SOLDERJUMPER | SOLDERJUMPER | working:SOLDERJUMPER_ARROW_NOPASTE |  |  |  | 
| SW2, SW3 | 2 | KMR2 | SWITCH_TACT_SMT4.6X2.8 | working:BTN_KMR2_4.6X2.8 |  |  |  | 
| TP1 | 1 | TESTPOINTROUND1.5MMNO | TESTPOINTROUND1.5MMNO | working:TESTPOINT_ROUND_1.5MM_NO |  |  |  | 
| U2 | 1 | AP2112K-3.3 | VREG_SOT23-5 | working:SOT23-5 |  |  |  | 
| U5 | 1 | 8MB QSPI Flash | SPIFLASH_8PIN_4X4 | working:USON8_4X4 |  |  |  | 
| U$34, U$35 | 2 | FIDUCIAL_1MM | FIDUCIAL_1MM | working:FIDUCIAL_1MM |  |  |  | 
| X6 | 1 | USB TYPE C | USB_C | working:USB_C_CUSB31-CFM2AX-01-X |  |  |  | 
| Y1 | 1 | 12MHZ | CRYSTAL2.5X2.0 | working:CRYSTAL_2.5X2 |  |  |  |

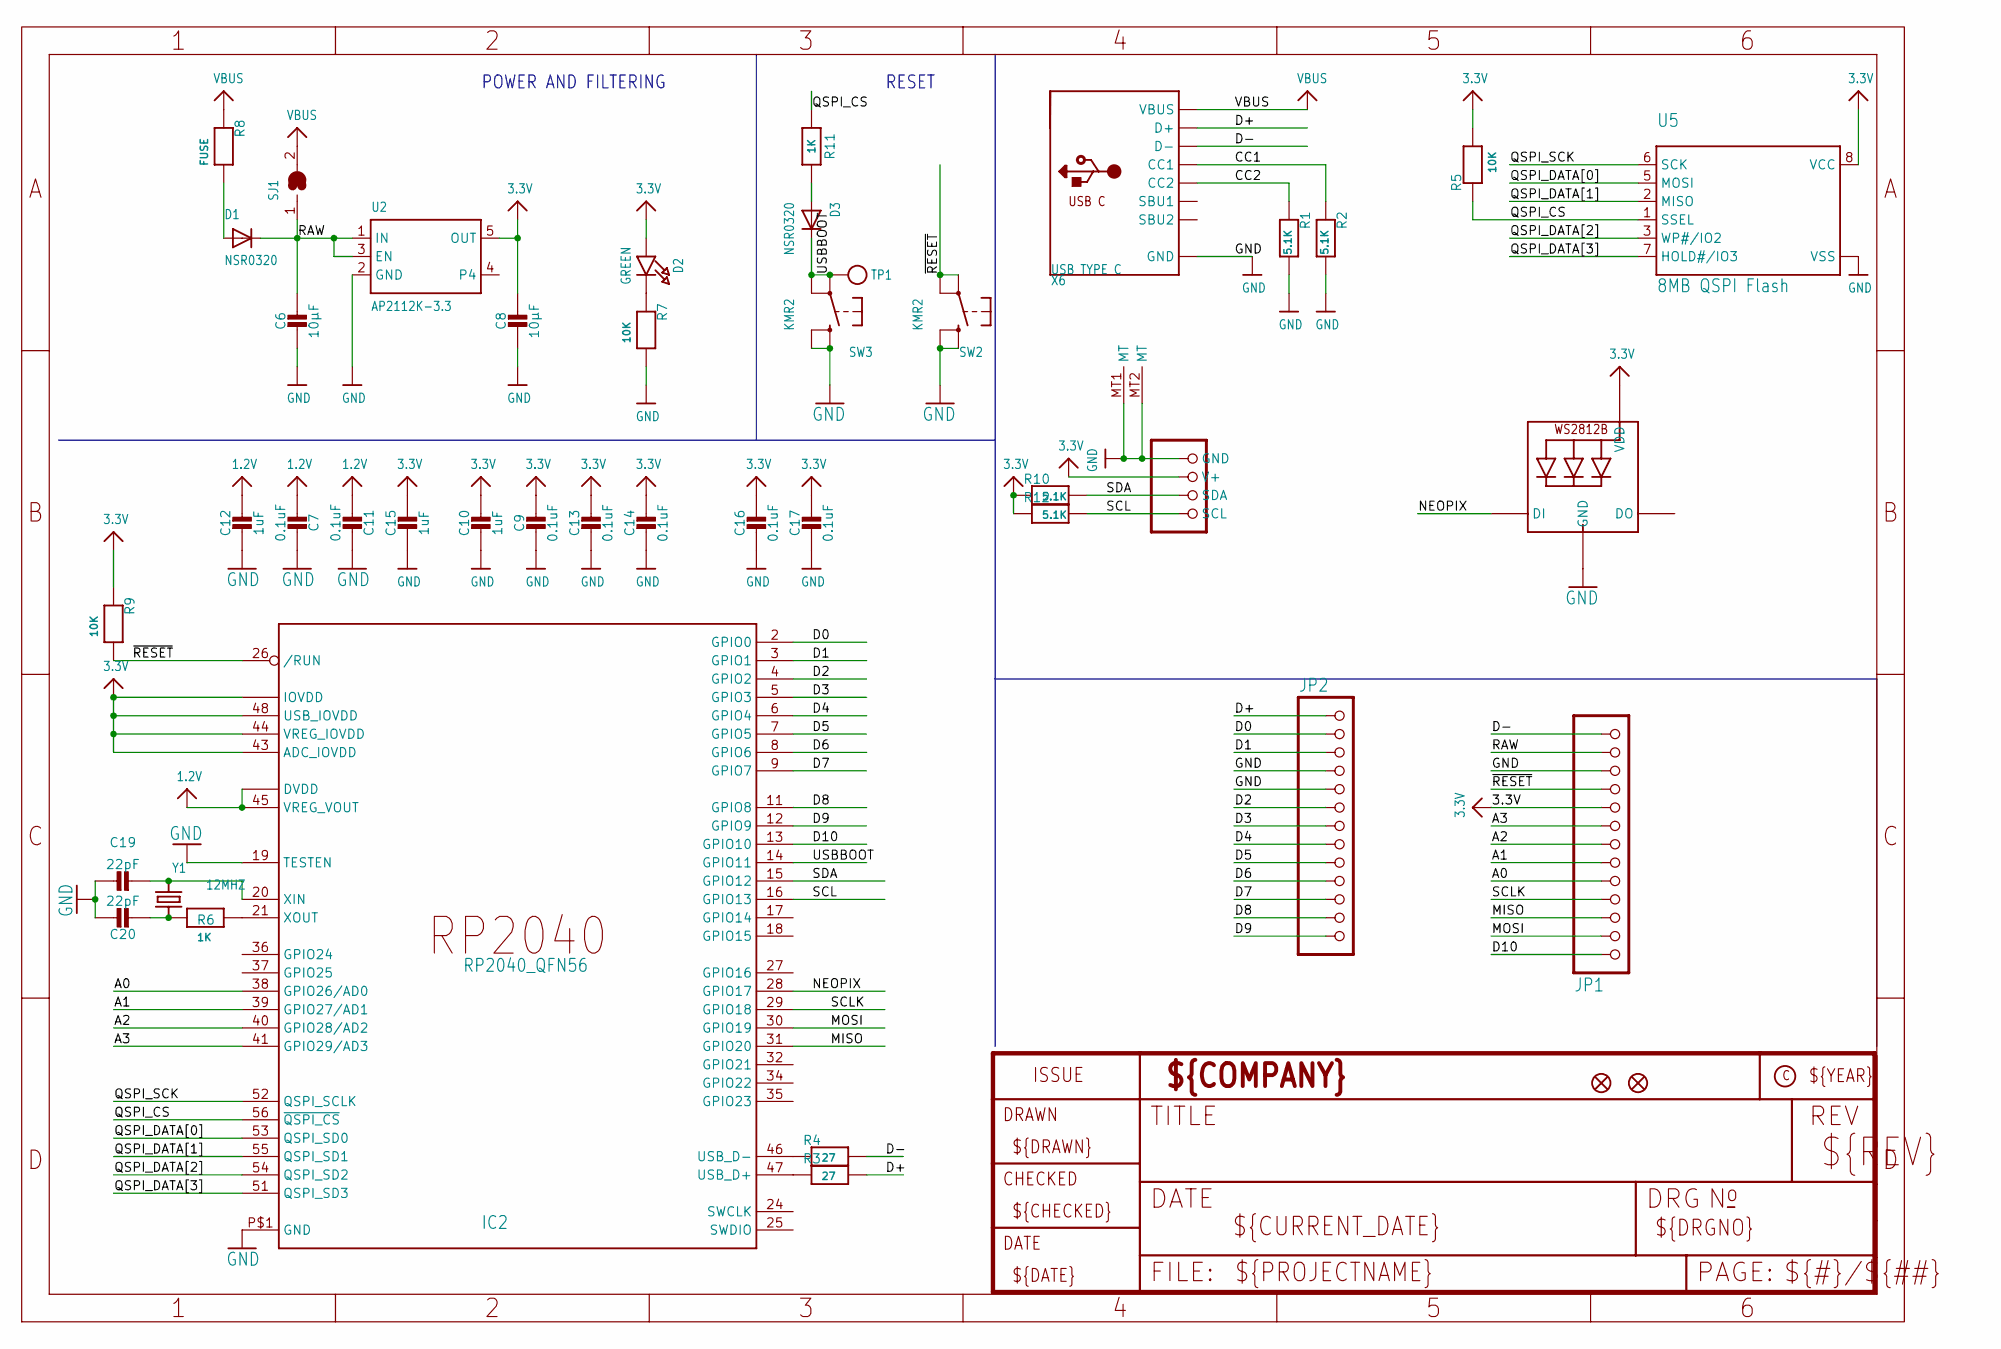
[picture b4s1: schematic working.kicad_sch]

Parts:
C6, C8: 10µF; _0805MP
C7, C9, C11, C13, C14, C16, C17: 0.1uF; _0402NO
C10, C12: 1uF; _0603MP
C15: 1uF; 0603-NO
C19, C20: 22pF; _0402NO
CONN1: STEMMA_I2C_QTSKINNY; JST_SH4_SKINNY
D1, D3: NSR0320; SOD-323F
D2: GREEN; CHIPLED_0603_NOOUTLINE
IC2: RP2040_QFN56; QFN56_7MM_REDUCEDEPAD
JP1, JP2: HEADER-1X13_CASTEL; 1X13_CASTEL
LED1: WS2812B_SK6805_1515; SK6805_1515
R1, R2, R10, R12: 5.1K; _0402NO
R3, R4: 27; _0402NO
R5, R7, R9: 10K; _0402NO
R6, R11: 1K; _0402NO
R8: FUSE; 0805-NO
SJ1: SOLDERJUMPER; SOLDERJUMPER_ARROW_NOPASTE
SW2, SW3: KMR2; BTN_KMR2_4.6X2.8
TP1: TESTPOINTROUND1.5MMNO; TESTPOINT_ROUND_1.5MM_NO
U2: AP2112K-3.3; SOT23-5
U5: 8MB QSPI Flash; USON8_4X4
U$34, U$35: FIDUCIAL_1MM
X6: USB TYPE C; USB_C_CUSB31-CFM2AX-01-X
Y1: 12MHZ; CRYSTAL_2.5X2

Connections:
1.2V: C7.2, C11.2, C12.1, IC2.23 (DVDD), IC2.45 (VREG_VOUT), IC2.50 (DVDD)
3.3V: C8.1, C9.1, C10.1, C13.1, C14.1, C15.1, C16.1, C17.1, CONN1.2 (V+), D2.A, IC2.1 (IOVDD), IC2.10 (IOVDD), IC2.22 (IOVDD), IC2.33 (IOVDD), IC2.42 (IOVDD), IC2.43 (ADC_IOVDD), IC2.44 (VREG_IOVDD), IC2.48 (USB_IOVDD), IC2.49 (IOVDD), JP1.9, JP1.9C (9), LED1.2 (VDD), R5.2, R9.1, R10.1, R12.1, U2.5 (OUT), U5.8 (VCC)
A0: IC2.38 (GPIO26/AD0), JP1.5, JP1.5C (5)
A1: IC2.39 (GPIO27/AD1), JP1.6, JP1.6C (6)
A2: IC2.40 (GPIO28/AD2), JP1.7, JP1.7C (7)
A3: IC2.41 (GPIO29/AD3), JP1.8, JP1.8C (8)
CC1: R2.1, X6.A5 (CC1)
CC2: R1.1, X6.B5 (CC2)
D0: IC2.2 (GPIO0), JP2.2, JP2.2C (2)
D1: IC2.3 (GPIO1), JP2.3, JP2.3C (3)
D2: IC2.4 (GPIO2), JP2.6, JP2.6C (6)
D3: IC2.5 (GPIO3), JP2.7, JP2.7C (7)
D4: IC2.6 (GPIO4), JP2.8, JP2.8C (8)
D5: IC2.7 (GPIO5), JP2.9, JP2.9C (9)
D6: IC2.8 (GPIO6), JP2.10, JP2.10C (10)
D7: IC2.9 (GPIO7), JP2.11, JP2.11C (11)
D8: IC2.11 (GPIO8), JP2.12, JP2.12C (12)
D9: IC2.12 (GPIO9), JP2.13, JP2.13C (13)
D10: IC2.13 (GPIO10), JP1.1, JP1.1C (1)
D+: JP2.1, JP2.1C (1), R3.2, X6.A6 (D+), X6.B6 (D+)
D-: JP1.13, JP1.13C (13), R4.2, X6.A7 (D-), X6.B7 (D-)
GND: C6.2, C7.1, C8.2, C9.2, C10.2, C11.1, C12.2, C13.2, C14.2, C15.2, C16.2, C17.2, C19.1, C20.1, CONN1.1 (GND), CONN1.MT1 (MT), CONN1.MT2 (MT), IC2.19 (TESTEN), IC2.P$1 (GND), JP1.11, JP1.11C (11), JP2.4, JP2.4C (4), JP2.5, JP2.5C (5), LED1.4 (GND), R1.2, R2.2, R7.2, SW2.B (S), SW2.B' (S1), SW3.B (S), SW3.B' (S1), U2.2 (GND), U5.4 (VSS), U5.PAD (VSS), X6.A1B12 (GND), X6.B1A12 (GND)
MISO: IC2.31 (GPIO20), JP1.3, JP1.3C (3)
MOSI: IC2.30 (GPIO19), JP1.2, JP1.2C (2)
unnamed: IC2.47 (USB_D+), R3.1
unnamed: D2.C, R7.1
unnamed: IC2.46 (USB_D-), R4.1
unnamed: D3.A, R11.2
unnamed: C19.2, IC2.20 (XIN), Y1.3 (2)
unnamed: C20.2, R6.1, Y1.1
unnamed: IC2.21 (XOUT), R6.2
unnamed: D1.A, R8.2
NEOPIX: IC2.28 (GPIO17), LED1.1 (DI)
QSPI_CS: IC2.56 (~QSPI_CS), R5.1, R11.1, U5.1 (SSEL)
QSPI_DATA[0]: IC2.53 (QSPI_SD0), U5.5 (MOSI)
QSPI_DATA[1]: IC2.55 (QSPI_SD1), U5.2 (MISO)
QSPI_DATA[2]: IC2.54 (QSPI_SD2), U5.3 (WP#/IO2)
QSPI_DATA[3]: IC2.51 (QSPI_SD3), U5.7 (HOLD#/IO3)
QSPI_SCK: IC2.52 (QSPI_SCLK), U5.6 (SCK)
RAW: C6.1, D1.C, JP1.12, JP1.12C (12), SJ1.1, U2.1 (IN), U2.3 (EN)
SCL: CONN1.4 (SCL), IC2.16 (GPIO13), R12.2
SCLK: IC2.29 (GPIO18), JP1.4, JP1.4C (4)
SDA: CONN1.3 (SDA), IC2.15 (GPIO12), R10.2
USBBOOT: D3.C, IC2.14 (GPIO11), SW3.A, SW3.A' (P1), TP1.P$1
VBUS: R8.1, SJ1.2, X6.A4B9 (VBUS), X6.B4A9 (VBUS)
~RESET: IC2.26 (/RUN), JP1.10, JP1.10C (10), R9.2, SW2.A, SW2.A' (P1)

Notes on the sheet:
RESET
POWER AND FILTERING

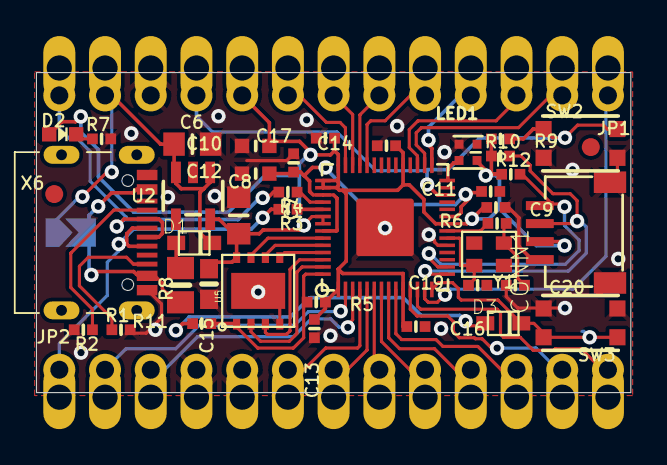
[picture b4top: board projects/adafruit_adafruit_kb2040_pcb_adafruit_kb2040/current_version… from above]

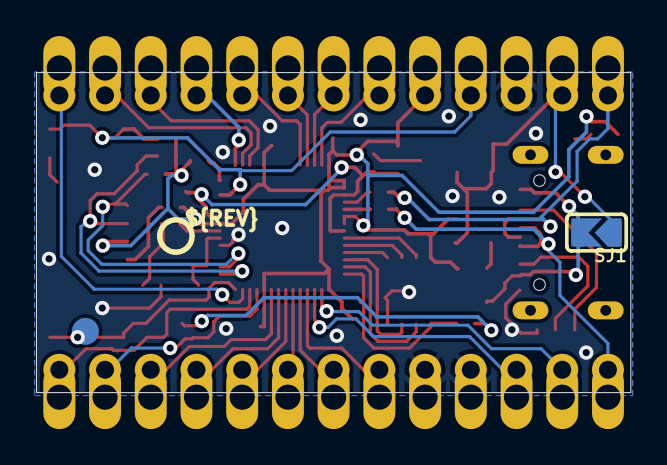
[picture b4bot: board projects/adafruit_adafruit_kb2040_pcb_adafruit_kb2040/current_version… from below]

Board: 4 copper layers, 33.0 x 17.8 mm, 47 parts (4 on the bottom side), 46 nets.

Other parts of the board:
U$17: KB2040_BOT
U$19: KB2040_TOP
U$20: PCBFEAT-REV-040

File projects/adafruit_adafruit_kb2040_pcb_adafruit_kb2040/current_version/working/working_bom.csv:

"Id";"Designator";"Footprint";"Quantity";"Designation";"Supplier and ref";
1;"R9,R5,R7";"_0402NO";3;"10K";;;
2;"C10,C12";"_0603MP";2;"1uF";;;
3;"Y1";"CRYSTAL_2.5X2";1;"12MHZ";;;
4;"D1,D3";"SOD-323F";2;"NSR0320";;;
5;"SW2,SW3";"BTN_KMR2_4.6X2.8";2;"KMR2";;;
6;"C8,C6";"_0805MP";2;"10µF";;;
7;"U2";"SOT23-5";1;"AP2112K-3.3";;;
8;"U$19";"KB2040_TOP";1;"";;;
9;"U5";"USON8_4X4";1;"8MB QSPI Flash";;;
10;"R10,R2,R1,R12";"_0402NO";4;"5.1K";;;
11;"IC2";"QFN56_7MM_REDUCEDEPAD";1;"RP2040_QFN56";;;
12;"R8";"0805-NO";1;"FUSE";;;
13;"U$34,U$35";"FIDUCIAL_1MM";2;"FIDUCIAL_1MM";;;
14;"R11,R6";"_0402NO";2;"1K";;;
15;"JP2,JP1";"1X13_CASTEL";2;"";;;
16;"C15";"0603-NO";1;"1uF";;;
17;"D2";"CHIPLED_0603_NOOUTLINE";1;"GREEN";;;
18;"C11,C17,C14,C7,C16,C13,C9";"_0402NO";7;"0.1uF";;;
19;"R3,R4";"_0402NO";2;"27";;;
20;"C19,C20";"_0402NO";2;"22pF";;;
21;"LED1";"SK6805_1515";1;"WS2812B_SK6805_1515";;;
22;"X6";"USB_C_CUSB31-CFM2AX-01-X";1;"USB TYPE C";;;
23;"CONN1";"JST_SH4_SKINNY";1;"STEMMA_I2C_QTSKINNY";;;
24;"SJ1";"SOLDERJUMPER_ARROW_NOPASTE";1;"";;;
25;"TP1";"TESTPOINT_ROUND_1.5MM_NO";1;"";;;
26;"U$17";"KB2040_BOT";1;"";;;
27;"U$20";"PCBFEAT-REV-040";1;"";;;
